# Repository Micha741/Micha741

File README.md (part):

# CircuitKit

Mobilní aplikace (React Native + Expo) pro elektroniky — databáze součástek, do budoucna
i návrh schémat obvodů a plošných spojů.

## Aktuální stav (MVP)

- **Databáze součástek** — lokální úložiště SQLite (`expo-sqlite`), běží celé na zařízení bez
  potřeby účtu nebo serveru.
  - Přidávání, úprava a mazání součástek
  - Pole: název, kategorie, výrobce, pouzdro, hodnota, počet kusů skladem, umístění,
    odkaz na datasheet, tagy, poznámky
  - Vyhledávání podle názvu / tagu / výrobce / hodnoty
  - Filtrování podle kategorie
  - **Výchozí knihovna běžných součástek** — při prvním spuštění se automaticky nahraje
    922 běžných součástek: 118 rezistorů (řada E12, 1 Ω – 8,2 MΩ; teplotní senzor Pt100; NTC
    termistory řady D-5 až D-25 pro omezení nárazového proudu; PTC termistory EPCOS/TDK
    B590** pro nadproudovou ochranu telekom linek; přesný tenkovrstvý SMD rezistor Yageo
    RT1206; obecná tlustovrstvá SMD čipová řada ROYALOHM (0201–2512, E-24/E-96); laserem
    in-circuit laditelná řada Susumu RT0603/RT0510/RT0816/RT1220; tenkovrstvá
    izolovaná rezistorová síť Vishay Dale TRA06E; kombinovaná rezistorová/kapacitní síť RCD
    Components RC0801-100J100J; a otočné potenciometry a trimry (lineární/logaritmické, THT/SMD)),
    51 kondenzátorů (keramické,
    elektrolytické, tantalové, fóliové; vysokonapěťová 1000V keramická disková řada NTE 90000;
    přesná keramická disková řada Multicomp MCBU/MCFU; nízko/vysokonapěťová keramická
    disková řada Illinois Capacitor GMR/GQR; NP0 disk Meritek CCNPO101J50V5B1; fóliová IGBT
    snubber řada Cornell Dubilier SCD; radiální tantalový kondenzátor RCD Components
    TRA10-103; vysokonapěťová 1250V fóliová řada Okaya HCPB; a širší vysokonapěťová fóliová řada
    Okaya HCP-S (450-1250V)), 232 diod
    (usměrňovací (včetně vysokonapěťové řady Diotec GP1120–GP1600, DO-41, 1200–6000V), spínací,
    Schottky (včetně extrémně malé 30V onsemi NSR01L30MX, pouzdro X3DFN2 0,62×0,32mm),
    Zenerovy (včetně SMD řady EIC SMZ25, SOD-123FL,
    3,0–200 V, 1,3 W, 46 hodnot),
    LED včetně výkonových SMD LED LUXEON Rebel, OSLON SSL 80, OSRAM TOPLED Black LO T64F/LR
    T66F (černé pouzdro pro VMS displeje) a OSRAM Mini TOPLED LY M67K, ploché LED displeje
    ROHM LD-201, LD-001 a LD-701, 7segmentové LED displeje AND Optoelectronics AND-5610,
    16segmentové
    alfanumerické displeje AND-8010-B a Yellow Stone BS-AA21RD/BS-CA21RD, Texas Instruments
    TIL302/303/304, bargraf displeje QT Optoelectronics MV53164/MV54164/MV57164, modrý
    jednomístný displej Everlight ELS-512UBWA, 3místné displeje Yellow Stone
    BT-M511RD/BT-N511RD a Everlight ELT-511USOWA, velkoformátový 2,3" displej Everlight
    ELS-2326SYGWA, obousměrné přepěťové ochrany TRISIL
    STMicroelectronics
    SMTPA62-320/SMP-0SCMC/SMP100MC/SMP100LC/SMP75, tripolární TLP140/200/270 a aktivní
    přepěťová/nadproudová ochrana CLP200M, tyristory SemiWell SCD4C60S a WeEn TYN50W/TYN80W-1600T
    (1600V vysokonapěťové SCR), triak WeEn BTA330 (30A Hi-Com, TO220/D²PAK), laserové diody
    Roithner LaserTechnik QL85H6S-A/B/C, QL78I6S-A/B/C, QL78F6S-A/B/C, QL78J6S-A/B/C a
    QL85J6S-A/B/C-L, proudově omezující dioda Diotec CL05M6F (5,6mA, SOD-123FL), a výkonový
    duální modul rychlých epitaxních diod IXYS DSEI 2x 61-04C/-06C (FRED, 2x60A, 400/600V,
    trr=35ns, miniBLOC/SOT-227B); SMD MiniMELF spínací diody Diotec LL4148/LL4150/LL4151/
    LL4448 (150-300mA, 50-100V, SOD-80C, elektrický ekvivalent 1N4148/1N4448 v DO-35); a SMD
    čipové (chip) diody DC Components CD4148W/CD4148WS/CD4148WT (1206/0805/0603, 100V/150mA,
    další ekvivalent 1N4148); a 7dílná řada SMD usměrňovacích diod se standardní dobou
    zotavení Diotec M1-M7 (50-1000V, 1A, SMA/DO-214AC, budget verze řady S1A-S1M); a duální
    (2 diody, společná katoda) SOT-23 diody Diotec BAV99/BAV99L (rychlé přepínání, trr<4ns,
    85/100V) a BAV199 (extrémně nízký svodový proud, IR<5nA); a výkonové šroubovací
    tyristorové moduly Semikron SEMIPACK 1 SKKT92 (2x SCR společná katoda), SKKT92B (2x SCR
    společná anoda) a SKKH92 (SCR+dioda, poloviční řízení), 800-1800V, ITAV 95A)), 19 můstků
    (SMD jednofázové usměrňovací můstky Diotec ABS2/ABS4/ABS6/ABS8/ABS10/ABS10-16, 200-1600V,
    pouzdro ABS; Diotec S40/S80/S125/S250/S380/S500, 80-1000V, pouzdro TO-269AA MiniDIL SLIM;
    a Fairchild/onsemi DF005S/DF01S/DF02S/DF04S/DF06S/DF08S/DF10S, 50-1000V/1,5A, pouzdro SDIP
    4L),
    86 tranzistorů (bipolární NPN/PNP (včetně onsemi rodiny BC817-16L/25L/40L, SOT-23), Darlington, duální, komplementární páry, výkonové, VF,
    MOSFET (včetně vysokonapěťového 600V/20A ISC H5N6001P, TO-3P, a duálního logic-level Nexperia BSS138PS, SOT363), IGBT (onsemi AFGB40T65SPD-BW,
    650V/40A Field Stop Trench, D²PAK, copackovaná rychlá dioda), JFET (včetně RF JFET rodiny
    Fairchild 2N5484/5485/5486 a SMD MMBF5484/5485/5486, SOT-23), IR fototranzistory Lite-On
    LTR-306 a LTR-1650D, fototranzistor pro viditelné
    světlo (náhrada CdS) Kodenshi PT23GP11), 170 integrovaných obvodů
    (časovače, komparátory, op-zesilovače, regulátory, logická hradla, čítače,
    Wi-Fi mikrokontroléry ESP32, ESP32-C3, ESP8285, ESP8684, Wi-Fi adaptér ESP8089, 8bit AVR
    mikrokontroléry ATmega640/1280/1281/2560/2561, rodina CAN mikrokontrolérů AT90CAN32/64/128
    (AVR) a T89C51CC01/02, AT89C51CC03 (8051), digitální teploměry DS18B20, DS1822, TC625,
    senzory vlhkosti a teploty DHT11, SHT71/SHT75, SHT85, CO2 senzory Sensirion SCD40/SCD41
    a kanálový (duct) senzor Belimo
    22DTH-51M, sériové flash paměti MX25L6406E a MX25L1026E, paralelní flash paměti řady
    MX29GL320E (T/B/H/L), USB-I2C most FT200XD, RS-485/RS-422 přijímače Renesas ISL32173E
    a příbuzné (ISL32175E/32177E/32273E/32275E/32277E), automotive TFT-LCD napájecí obvody
    Maxim MAX25220/MAX25221/MAX25221B/MAX25520, LCD-TV napájecí obvody Intersil/Renesas
    ISL97652 a ISL78010, TFT-LCD napájecí obvody E-CMOS EC9223 a Torex XC9516, senzory
    vlhkosti/teploty HOPERF TH10, PIR pohybové senzory Murata IRA-S410ST03, IRA-S230ST01 a
    kvadrátní IRA-S510ST01, plynový (SnO2) senzor ozónu Hanwei MQ-131, I2C senzory LITE-ON
    LTR-706PS-01 (proximity s VCSEL emitorem) a LTR-329ALS-01 (okolní osvětlení, duální kanál),
    piezoelektrické rázové/vibrační senzory Murata PKGS-00LDP1-R,
    PKGS-25WXP1-R a automotive TPMS PKGS-45TAV-R, zesilovací IC pro rázový senzor ROHM
    BD3852MUZ-Z, 6osý MEMS akcelerometr/gyroskop STMicroelectronics LSM330DL, jednoosý
    analogový křemenný automotive gyroskop Epson Toyocom XV-8000CB, a galvanicky oddělené
    proudové senzory ZMC10 (magnetorezistivní) a Allegro ACS752SCA-050/ACS754xCB-050/
    ACS754xCB-150/ACS755xCB-050 (Hallův jev), reflexní optický senzor Honeywell
    HOA0709-011, optické PPG senzory OSRAM SFH 7051 (tepová frekvence), SFH7050
    (tepová frekvence + SpO2) a SFH7060 (5 emitorů, tepová frekvence + SpO2), a proudové
    senzory CUI CSXX05B series aj.; izolovaný DC/DC měnič TRACO POWER TRA 1 Series; fototranzistorové
    optočleny LITE-ON LTV-356T (CTR 50-600%, Viso 3750Vrms, mini-flat SMD), Everlight EL817
    Series (CTR 50-600%, Viso 5000Vrms, DIP-4/SMD), Sharp PC817 Series (rank A-D, CTR 50-600%,
    Viso 5000Vrms, DIP-4), dvoukanálová řada Vishay ILD205T/206T/207T/211T/213T/217T (2 optočleny
    v pouzdře SOIC-8, BVCEO 70V, Viso 3000Vrms) a LITE-ON LTV-8X7 Series (LTV-817 1-kanálový
    DIP-4, LTV-827 2-kanálový DIP-8, LTV-847 4-kanálový DIP-16, Viso 5000Vrms, VCEO 35V);
    osmikanálové Darlingtonovy budiče ST ULN2801A/2802A/2803A/2804A (500mA/kanál, 50V, DIP-18,
    liší se vstupním odporovým děličem pro různé logické rodiny); hardwarový TCP/IP Ethernet
    kontrolér WIZnet W5500 (SPI, 32KB buffer, 8 hardwarových socketů, LQFP-48); napěťové
    supervizory (reset obvody) TI TPS3809J25/L30/K33/I50 (prahy 2,25/2,64/2,93/4,55V, SOT-23-3,
    pin-kompatibilní s MAX809); nízkopříkonový CMOS časovač ST TS555 (pinově kompatibilní s
    NE555, 110µA typ., max. 2,7MHz); 16bitový nízkopříkonový MCU TI MSP430G2553 (16KB Flash,
    512B RAM, ADC10, USCI UART/SPI/I2C, základ LaunchPad kitu); 32bitový Arm Cortex-M0+ MCU
    TI MSPM0L1306 (64KB Flash, 4KB RAM, 12bit 1,68Msps ADC, 2x OPA, GPAMP, COMP, UART/I2C/SPI);
    starší 16bitový MCU TI MSP430F149 (60KB Flash, 2KB RAM, ADC12, 2x USART, hardwarová
    násobička, 48 I/O); nejmenší MSP430 MSP430F1121A (4KB Flash, 256B RAM, 14 I/O, jen
    komparátor bez ADC, 20/24pinové pouzdro); z katalogu HOPERF Catalog 2020: RF vysílací/
    přijímací IC řada CMOSTEK CMT2xxx (27-1020MHz, OOK/(G)FSK/MSK), tlakové senzory HOPERF
    HPxxx/HP5xxx Series (300Pa-2000kPa, I2C/SPI) a levnější sesterské senzory vlhkosti/teploty
    TH08, TH06 a teplotní senzor T06 (SOT23-5, bez vlhkosti) k již evidovanému TH10; a plně
    digitální Class-D zesilovače reproduktoru s DSP ROHM BM28720MUV (20W+20W) a BM28723MUV
    (17W+17W, output feedback, bez snubberu); a digitální barometrický tlakový senzor Bosch
    BMP280 (I2C/SPI); kombinovaný digitální senzor vlhkosti/tlaku/teploty Bosch BME280
    (I2C/SPI, registrově kompatibilní s BMP280); neregulovaný izolovaný DC/DC měnič RECOM
    ECONOLINE REZ Series; trojitý single-supply video buffer s nábojovou pumpou Renesas/Intersil
    ISL59837 (16 Ld QSOP); 12dílná rodina LDO regulátorů NIKO-SEM L1117 (SOT-223/TO-220/TO-252/
    TO-263, pevné 2,5-5V i nastavitelné); 9dílná rodina nízkoproudých LDO regulátorů Fairchild
    KA78LXXA (TO-92, 5-24V); kompletní napájecí řadič pro DDR2/DDR3/DDR3L/LPDDR3 paměti Texas
    Instruments TPS51716 (buck + VTT LDO + VTTREF, 20-pin QFN); 1/4" SOC VGA NTSC/PAL CMOS
    obrazový senzor Micron MT9V135C12STC (48-pin CLCC, kompozitní video/LVDS/CCIR656); a
    kombinovaný PFC + half-bridge řadič předřadníku zářivek International Rectifier IRS2580DSPbF
    ("COMBO8", 8pin SOIC); a napájecí spínač (load switch) se soft-startem onsemi NCP330MUTBG
    (RDS(on) 26mΩ, 3A, UDFN4)),
    161 modulů
    (Wi-Fi/BLE: ESP32-C3-MINI-1, ESP32-C3-WROOM-02, Adafruit Feather
    HUZZAH ESP8266, ESP8684-MINI-1, ESP-12S; nízkonapěťové odpojovače baterie Alfatronix
    PowerTector PT10/PT20/PT40/PT60/PT100/PT200; LoRaWAN senzor LEO-S55 a brány USM-S67;
    solární bezdrátové senzory EnOcean ETHSA/ETHSU; 6,86" IPS TFT LCD moduly AZ Displays
    ATM0680L2A-CT s kapacitním dotykem a ATM0680L2A bez dotyku; a polohové displeje vřetene
    Baumer IVO N 142/N 152; znakový LCD modul PICVUE PVC200403; křemenné tlakové senzory
    Seiko Epson TSU-20G/TSU-70G/TSU-100G; evaluační deska ROHM RPR-0521RS-EVK-001 pro
    kombinovaný senzor přiblížení/okolního osvětlení; optoelektronické snímače přiblížení SICK
    WTB250-2N1131/WTB250-2N1151; wearable zdravotní senzorový náramek Maxim MAXREFDES103#
    s optickým PPG biosenzorem; MEMS tlakový senzorový modul Hokuriku HPM-100GD-A01; a
    indukční přibližovací spínače TURCK BI1.5U-EG08-RP6X-H1341 (uprox Factor 1) a
    BI1-EG05K-AN6X-V1331 (klasický feritový); radarové senzory pohybu Banner R-GAGE
    Q130RA (FMCW) a Pepperl+Fuchs RaDec-M, RAVE-D-NA, RMS-G-RC a RMS-M-RC (Dopplerovy, relé
    výstup(y), rozlišení osob/vozidel u RAVE-D-NA/RMS-G-RC); a kapacitní přibližovací
    spínače TURCK BC10-PT30-AZ3X, BC10-Q14-VN4X2,
    BC10-QF5.5-RN6X2, BC20-Q20-RZ3X2, BC20-Q20-AN4X2/S400 (DC verze, kabel) a
    BC20-Q20-AN4X2-H1141 (DC verze, M12 konektor); a indukční přibližovací spínač Pepperl+Fuchs
    NBB1-4GM22-E0, NBB2-8GM25-E0-V3, NBB2-8GM25-E2-V3, NBB2-8GM40-E2-V1, NBB2-8GM50-E0,
    NBB2-8GM50-E2-5M, NBB2-8GS35-E2-V1, NBB2-8GS40-E2-5M-PUR, NBB2-12GM60-A2, NBB3-V3-Z4,
    NBB4-12GM30-E2-V3, NBB4-12GM30-E3, NBB4-12GM35-A2-V1-M1 (automotive),
    NBB4-12GM50-E2-3G-3D (ATEX), NBB4-12GM75-US, NBB5-18GM40-Z0-V1, NBB8-18GM50-E2,
    NBB10-30GM50-E0, NBB10-30GM50-E2-C3-V1, NBB20-L3M-A2-C3-V1 (svařovací "Weld Immune") a
    NBB20-U1-A2-T (otočná hlava, VariKont), NBN3-F31K-E8-K (dvoukanálová jednotka pro
    pneumatické pohony s výstupem pro solenoidový ventil), NEN6-8GM40-E2-PUR (nezápustný
    typ), NBB8-18GM50-A0-V1-M1 (automotive M18), NBB15-30GM50-E0-M-Y242746 (M30, NPN, E1
    homologace, -40 až +85 °C), NBN8-12GM50-E2-V1-Y323749 (nezápustný M12, konektor) a
    NBN40-U1-E0-M (otočná hlava VariKont, 40mm, nezápustný, E1, 10-60V) a
    NJ4-12GM-N-5M-Y123257 (NAMUR výstup, ATEX jiskrově bezpečný, zóna 20); a kapacitní přibližovací
    spínače Pepperl+Fuchs CBB4-12GH60-E0-V1 (potravinářský, nerez 316L, NPN) a CBB4-12GH60-E2-V1
    (potravinářský, nerez 316L, PNP) a CBB8-18GS75-E2 (M18, nastavitelný rozsah 1-8mm, kabel);
    a fotoelektrická jednocestná závora
    (through-beam pár vysílač+přijímač) SICK GRSE18S-N2421V (GR18 Inox); reflexní fotoelektrický
    senzory s IO-Link Pepperl+Fuchs OBG4000-R103-2EP-IO, OBG5000-R100-EP-IO-V3 a
    OBG5000-R101-2EP1-IO (detekce transparentních objektů); a MIPI CSI-2 kamerový
    modul Leopard Imaging LI-OS05A20-MIPI-110H (OmniVision OS05A20, 5 Mpx); průmyslový vizuální
    senzor (smart kamera) Festo SBSC-U-AF-R2B (čtení kódů, OCR, Ethernet), vizuální senzor pro
    polohování regálových zakladačů Pepperl+Fuchs PHA400-F200A-B17-V1D a PHA400-F200-B17-V1D
    (PROFINET, liší se jen orientací konektorů) a barevný vizuální
    senzory Festo SBSI-F-R3C-F6-W a SBSI-F-AF-R3C-F12-W (integrovaná optika/osvětlení, plná
    kapacita) a monochromní objektový senzor Festo SBSI-Q-AF-R2B-F12-W; a polohové snímače
    pístu pneumatického válce Festo SME-8M-DS-24V-K-5,0-OE (magnetický jazýčkový kontakt),
    SMT-8M-A-PS-24V-E-0,3-M8D, SMT-8M-A-PS-24V-E-2,5-OE, SMT-8M-A-PS-24V-E-0,3-M12
    (magnetorezistivní) a SMT-8M-A-ZS-24V-E-5,0-OE-EX2 (magnetorezistivní, ATEX, 2vodičové), a
    svařovací pole odolný Festo SDBT-BSW-1L-PU-W-0.3-N-M12 (magnetorezistivní, weld-resistant) a
    SME-8-K5-LED-24 (reed, podélné upnutí, otevřený konec kabelu) a SME-8-S-LED-24 (reed,
    podélné upnutí, M8 konektor), SMEO-8E-K-24-S6 (reed, vysokoteplotní -40 až +120 °C, montáž
    příslušenstvím), SMEO-8E-M12-LED-24 (reed, integrovaný konektor M12, hliníkové pouzdro) a
    SMEO-8E-M12-LED-230 (reed, integrovaný konektor M12, univerzální 3-230V AC/3-250V DC) a
    SMPO-8E (čistě pneumatický 3/2 ventil bez elektrického připojení, ATEX zóny 1/2/21/22) a
    SMTSO-8E-NS-M12-LED-24 (magnetoindukční, NPN, svařovací pole odolný) a
    SMT-10G-PS-24V-E-2,5Q-OE (magnetorezistivní, pro kruhovou drážku) a
    SME-10M-ZS-24V-E-2,5-Q-OE (reed, 2vodičové, pro kruhovou drážku) a Festo SIEH-3B-PS-S-L
    (obecný miniaturní indukční spínač Ø3 mm) a SPAN-B11R-M5F-PNLK-PNVBA-L1 (tlakový senzor s
    displejem, IO-Link), SPAN-B-B11R-R18M-PN-L1+2.5S (tlakový senzor s displejem, "Basic",
    1 výstup), SDE5-D10-C3-Q6E-P-K (tlakový spínač bez displeje, QS-6, integrovaný kabel) a
    SDE5-D10-C-Q4E-P-M8 (tlakový spínač bez displeje, QS-4, M8 konektor) a SDE5-D10-NF-Q6E-V-K
    (analogový tlakový snímač 0-10V, bez spínacího výstupu, integrovaný kabel) a
    SDE5-D10-NF-Q6E-V-M8 (analogový tlakový snímač 0-10V, M8 konektor), SDE5-D10-O-Q6E-P-M8
    (tlakový spínač bez displeje, N/O, QS-6, M8) a SDE5-V1-NF-Q6-V-M8 (analogový vakuový snímač
    0 až -1 bar, M8) a SPAN-B11R-M5F-PN-PN-L1 (tlakový senzor s displejem, 2 výstupy, bez
    analogu a IO-Link), SPAW-P100R-G12M-2N-M12 (vysokotlaký tenkovrstvý senzor 0-100 bar,
    celokovový), SPAW-B11R-G14F-2P-M12 (tenkovrstvý senzor -1 až 10 bar, celokovový) a
    SPAW-B2R-G12M-2P-M12 (piezorezistivní senzor -1 až 1 bar, celokovový) a
    SPAW-B11R-G14F-2N-M12 (tenkovrstvý senzor -1 až 10 bar, celokovový, NPN) a
    SPAW-P100R-G14F-2N-M12 (vysokotlaký tenkovrstvý senzor 0-100 bar, celokovový, G1/4) a
    SPAW-P50R-G12M-2N-M12 (vysokotlaký tenkovrstvý senzor 0-50 bar, celokovový),
    SPAW-P25R-G12M-2NV-M12 (0-25 bar, spínací + analogový výstup současně), optický senzor
    prachu/PM2.5 Winsen ZPH02 a ATEX senzorová skříň polohy ventilu Festo
    SRBE-CA3-YR90-MW-22A-1W-C2M20-EX (mechanický přepínací spínač), RGB segment signálního
    majáku Banner SG-TL70-RGB14, programovatelný zvukový segment Banner SG-TL70-AP (MP3/WAV) a
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
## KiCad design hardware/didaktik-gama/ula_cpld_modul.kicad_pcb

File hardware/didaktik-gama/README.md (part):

# Didaktik Gama – schéma zapojení v KiCadu

Překresleno z tištěné předlohy „DIDAKTIK GAMA – SCHÉMA ZAPOJENIA“.

| Soubor | Obsah |
|---|---|
| `didaktik_gama.kicad_pcb` | plošný spoj hlavní desky 300 × 225 mm, 4 vrstvy – rozmístěno, nety přiřazeny, **cesty signálů zatím nevedené** |
| `didaktik_gama_pcb_nahled.pdf` | náhled rozmístění desky |
| `gen_pcb.py` | generátor desky z `netlist.py` (`python3 gen_pcb.py`, potřebuje KiCad s modulem pcbnew) |
| `ula_cpld_modul.kicad_pcb` / `_pcb_nahled.pdf` | plošný spoj modulu ULA 70 × 50 mm, 2 vrstvy – rozmístěno, nety přiřazeny, cesty nevedené |
| `gen_pcb_modul.py` | generátor desky modulu (`python3 gen_pcb_modul.py`) |
| `make_fab.py` | výrobní podklady: gerbery, vrtání, soupis součástek, souřadnice osazení, ZIP (do `vyroba/`) |
| `gama.pretty/`, `fp-lib-table` | vlastní pouzdro Raspberry Pi Pico (THT 2×20) |
| `didaktik_gama.kicad_sch` / `.kicad_pro` | schéma pro KiCad 8 a novější (A0, jedna strana, vlastní knihovna symbolů je v souboru) |
| `didaktik_gama_nahled.pdf` / `.svg` | náhled bez KiCadu |
| `netlist.csv` | všechny nety a piny (`U1.30` = U1 pin 30) |
| `bom.csv` | soupis součástek |
| `k_overeni.csv` | místa, která jsou na předloze nečitelná nebo odhadnutá |
| `netlist.py` | **zdroj pravdy** – netlist ručně přepsaný z předlohy |
| `gen.py` | generátor: `python3 gen.py` vše znovu vytvoří, `python3 gen.py modul` vytvoří modul ULA |
| `ula_cpld_modul.kicad_sch` / `.kicad_pro` / `_nahled.pdf` | modul náhrady ULA s CPLD XC95144XL (TQ100) do patice U4 |
| `ula_cpld_modul.ucf` | přiřazení pinů CPLD pro firmware (Xilinx ISE) |
| `netlist_modul.py`, `*_modul.csv` | netlist, soupis a body k ověření modulu |

Spoje jsou vedeny návěštími (labels): stejné jméno = stejný net. `/X` v netlistu
(v KiCadu `~{X}`) znamená signál aktivní v nule. Oprava spoje = změna jména netu
v `netlist.py` a nové spuštění `gen.py`, nebo přejmenování návěští přímo v KiCadu.

Napájení (konektor J5, pojistka F1, ochranná dioda D12, MA7805 U32, filtrace a blokovací
kondenzátory 100n u každého IC) na předloze není – je doplněno a vedeno v `k_overeni.csv`.

Pinouty UA880D, 27128, 8255, 4164, 2118 a 74LS157 odpovídají katalogovým listům
a souhlasí s čísly na předloze. ULA je očíslovaná podle předlohy (shodné se ZX ULA).

## Plošný spoj hlavní desky
- **Rozměr 300 × 225 mm, 4 vrstvy:** F.Cu a B.Cu pro signály, In1.Cu = celoplošná **GND**, In2.Cu =
  celoplošná **+5V**. Napájení všech vývodových součástek je tím propojené bez cest.
- **Rozmístění po blocích:** konektory na horním okraji (napájení, MG, jack, reproduktor, VGA,
  klávesnice, porty 8255) → CPU / ROM / 8255 / patice ULA → multiplexery a logika → 8× 4164 →
  8× 2118 → zvuk (YM2149, LM386), USB klávesnice (Pico), napájení. Blokovací kondenzátory u každého IC.
- **Kontrola DRC:** žádné překryvy pouzder ani chyby obrysu; zbývá **499 nepropojených spojů** (cesty
  signálů + napájení SMD obvodů U40/U41, které potřebují prokovy do vnitřních vrstev).

### Dokončení (vedení cest)
1. Otevřít `didaktik_gama.kicad_pro` v KiCadu 8/9 (soubor desky je ve formátu KiCadu 7, otevře se).
2. Automaticky: **Freerouting** (plugin v KiCadu nebo File → Export → Specctra DSN, výsledek
   File → Import → Specctra Session). Pravidla: cesta 0,25 mm, mezera 0,2 mm, prokov 0,6/0,3 mm;
   napájecí cesty (VIN, SPK_OUT) ručně 0,6–1 mm.
3. Zkontrolovat orientaci konektorů na hraně (VGA, jack, napájecí konektor) ve 3D náhledu.
4. Po začátku vedení cest už **nespouštět `gen_pcb.py`** (přepíše desku) – změny ze schématu přenášet
   v KiCadu přes *Update PCB from Schematic*.

## Plošný spoj modulu ULA
- **70 × 50 mm, 2 vrstvy**, zem rozlitá z obou stran (F.Cu i B.Cu).
- **J1** = 40 kolíků v rozteči DIP-40 (600 mil), zespodu do patice U4; pin 1 vlevo dole (čtvercová ploška).
  Mezi řadami kolíků jsou SMD součástky (stabilizátor U2, oscilátor X1, odpory) – J1 má proto vymezení
  jen kolem řad kolíků. Použít precizní (soustružené) kolíky.
- **U1** XC95144XL (TQFP-100) nad horní řadou kolíků, blokovací kondenzátory u napájecích vývodů.
- **J2** vlevo (RGB + zvuk + napájení, kabel 1:1 na J8 hlavní desky), **J3** JTAG vpravo.
- Modul přesahuje patici: na hlavní desce zabírá plochu 70 × 50 mm nad U4. J8 je proto u pravé hrany;
  pod modulem smí být jen nízké součástky (odpory, keramické kondenzátory).
- DRC: bez překryvů; zbývá 76 nepropojených spojů (cesty) a 2 zemní plošky CPLD s jedním
  tepelným můstkem – vyřeší se při vedení cest (prokov k zemi u vývodu).

## Výrobní podklady (gerbery)
Až budou obě desky natrasované a DRC v KiCadu čisté:
```bash
python3 make_fab.py            # obě desky
python3 make_fab.py modul      # jen modul ULA
```
Vznikne `vyroba/<deska>/`: `<deska>_gerber.zip` (gerbery + vrtání, nahrát výrobci), `gerber/` (jednotlivé
vrstvy, mapy vrtání PDF, job soubor), `<deska>_bom.csv` (soupis ve formátu Comment/Designator/Footprint),
`<deska>_pozice.csv` (souřadnice pro strojní osazení) a `PARAMETRY.txt` (parametry objednávky).

**Pojistka:** skript nejdřív spustí DRC; pokud deska má nevedené cesty nebo chyby, export odmítne
(gerbery by daly nefunkční desku). `--force -o DIR` vytvoří zkušební export s varováním NEVYRÁBĚT.

| Deska | Parametry objednávky |
|---|---|
| hlavní | 300 × 225 mm, 4 vrstvy (In1 GND, In2 +5V), FR-4 1,6 mm, Cu 35 µm, HASL bezolovnatý / ENIG |
| modul ULA | 70 × 50 mm, 2 vrstvy, FR-4 1,6 mm, ENIG doporučeno (TQFP s roztečí 0,5 mm) |

## Návod pro Windows

### 1. Programy
| Program | K čemu | Odkud |
|---|---|---|
| **KiCad 10** (stabilní; případně 9) | schéma, desky, trasování, gerbery; obsahuje i Python s modulem `pcbnew`. **Ne vývojovou verzi 10.99** – ta Python/`pcbnew` nemá | https://www.kicad.org/download/windows/ |
| Git for Windows (volitelně) | stažení repozitáře, Git Bash pro skripty `.sh` | https://git-scm.com/download/win |
| Freerouting (volitelně) | automatické vedení cest – v KiCadu *Plugin and Content Manager* → „Freerouting“ | správce doplňků KiCadu |
| **Java 25+** (pro Freerouting) | Temurin JRE 25, Windows x64 .msi; v instalátoru zapnout *Set JAVA_HOME* a *Add to PATH*, pak restartovat KiCad (`java -version` musí ukázat 25+) | https://adoptium.net/temurin/releases/?version=25 |

Repozitář stáhněte přes *Code → Download ZIP* na GitHubu (nebo `git clone`) a rozbalte například do
`C:\gama`. Dále se pracuje ve složce `C:\gama\hardware\didaktik-gama`.

### 2. Dávkové soubory (dvojklik)
Soubory `.bat` samy najdou Python, který dodává KiCad (`C:\Program Files\KiCad\10.0`, `9.0` nebo `8.0`).

| Soubor | Co udělá |
|---|---|
| `vyroba.bat` | výrobní podklady do `vyroba\` (stejně jako `make_fab.py`; lze `vyroba.bat modul`, `vyroba.bat --force -o C:\test`) |
| `schema.bat` | znovu vytvoří schémata, netlisty, BOM a seznam k ověření z `netlist.py` / `netlist_modul.py` |
| `deska.bat` | znovu vytvoří obě desky z netlistu – **přepíše natrasované cesty**, proto se ptá |

Ručně lze totéž spustit z nabídky Start → **KiCad Command Prompt** (má v cestě `python` i `kicad-cli`):
```bat
cd /d C:\gama\hardware\didaktik-gama
python make_fab.py
```

### 3. Postup od desky k objednávce
1. Dvojklik na `didaktik_gama.kicad_pro` → otevře se KiCad; otevřít editor desky.
2. Trasování: *Tools → External Plugins → Freerouting* (nebo *File → Export → Specctra DSN*, ve Freeroutingu
   *Autorouter*, pak *File → Import → Specctra Session*). Totéž pro `ula_cpld_modul.kicad_pcb`.
3. *Inspect → Design Rules Checker* → opravit chyby, nepropojené spoje musí být 0.
4. Dvojklik `vyroba.bat` → ve `vyroba\hlavni\` a `vyroba\modul\` jsou ZIPy pro výrobce a `PARAMETRY.txt`.

### 4. Firmware na Windows
- **Pico (USB klávesnice a kazety):** instalátor *Raspberry Pi Pico* pro Windows nebo rozšíření
  *Raspberry Pi Pico* ve VS Code (obsahuje Pico SDK, CMake a překladač). Otevřít složku
  `firmware\pico-usb-kbd`, přeložit, `gama_usb_kbd.uf2` zkopírovat na disk RPI-RP2 (Pico s BOOTSEL).
  Testy na PC (`test\run_tests.sh`) jdou v Git Bash s překladačem `gcc` (např. z MSYS2) nebo ve WSL.
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
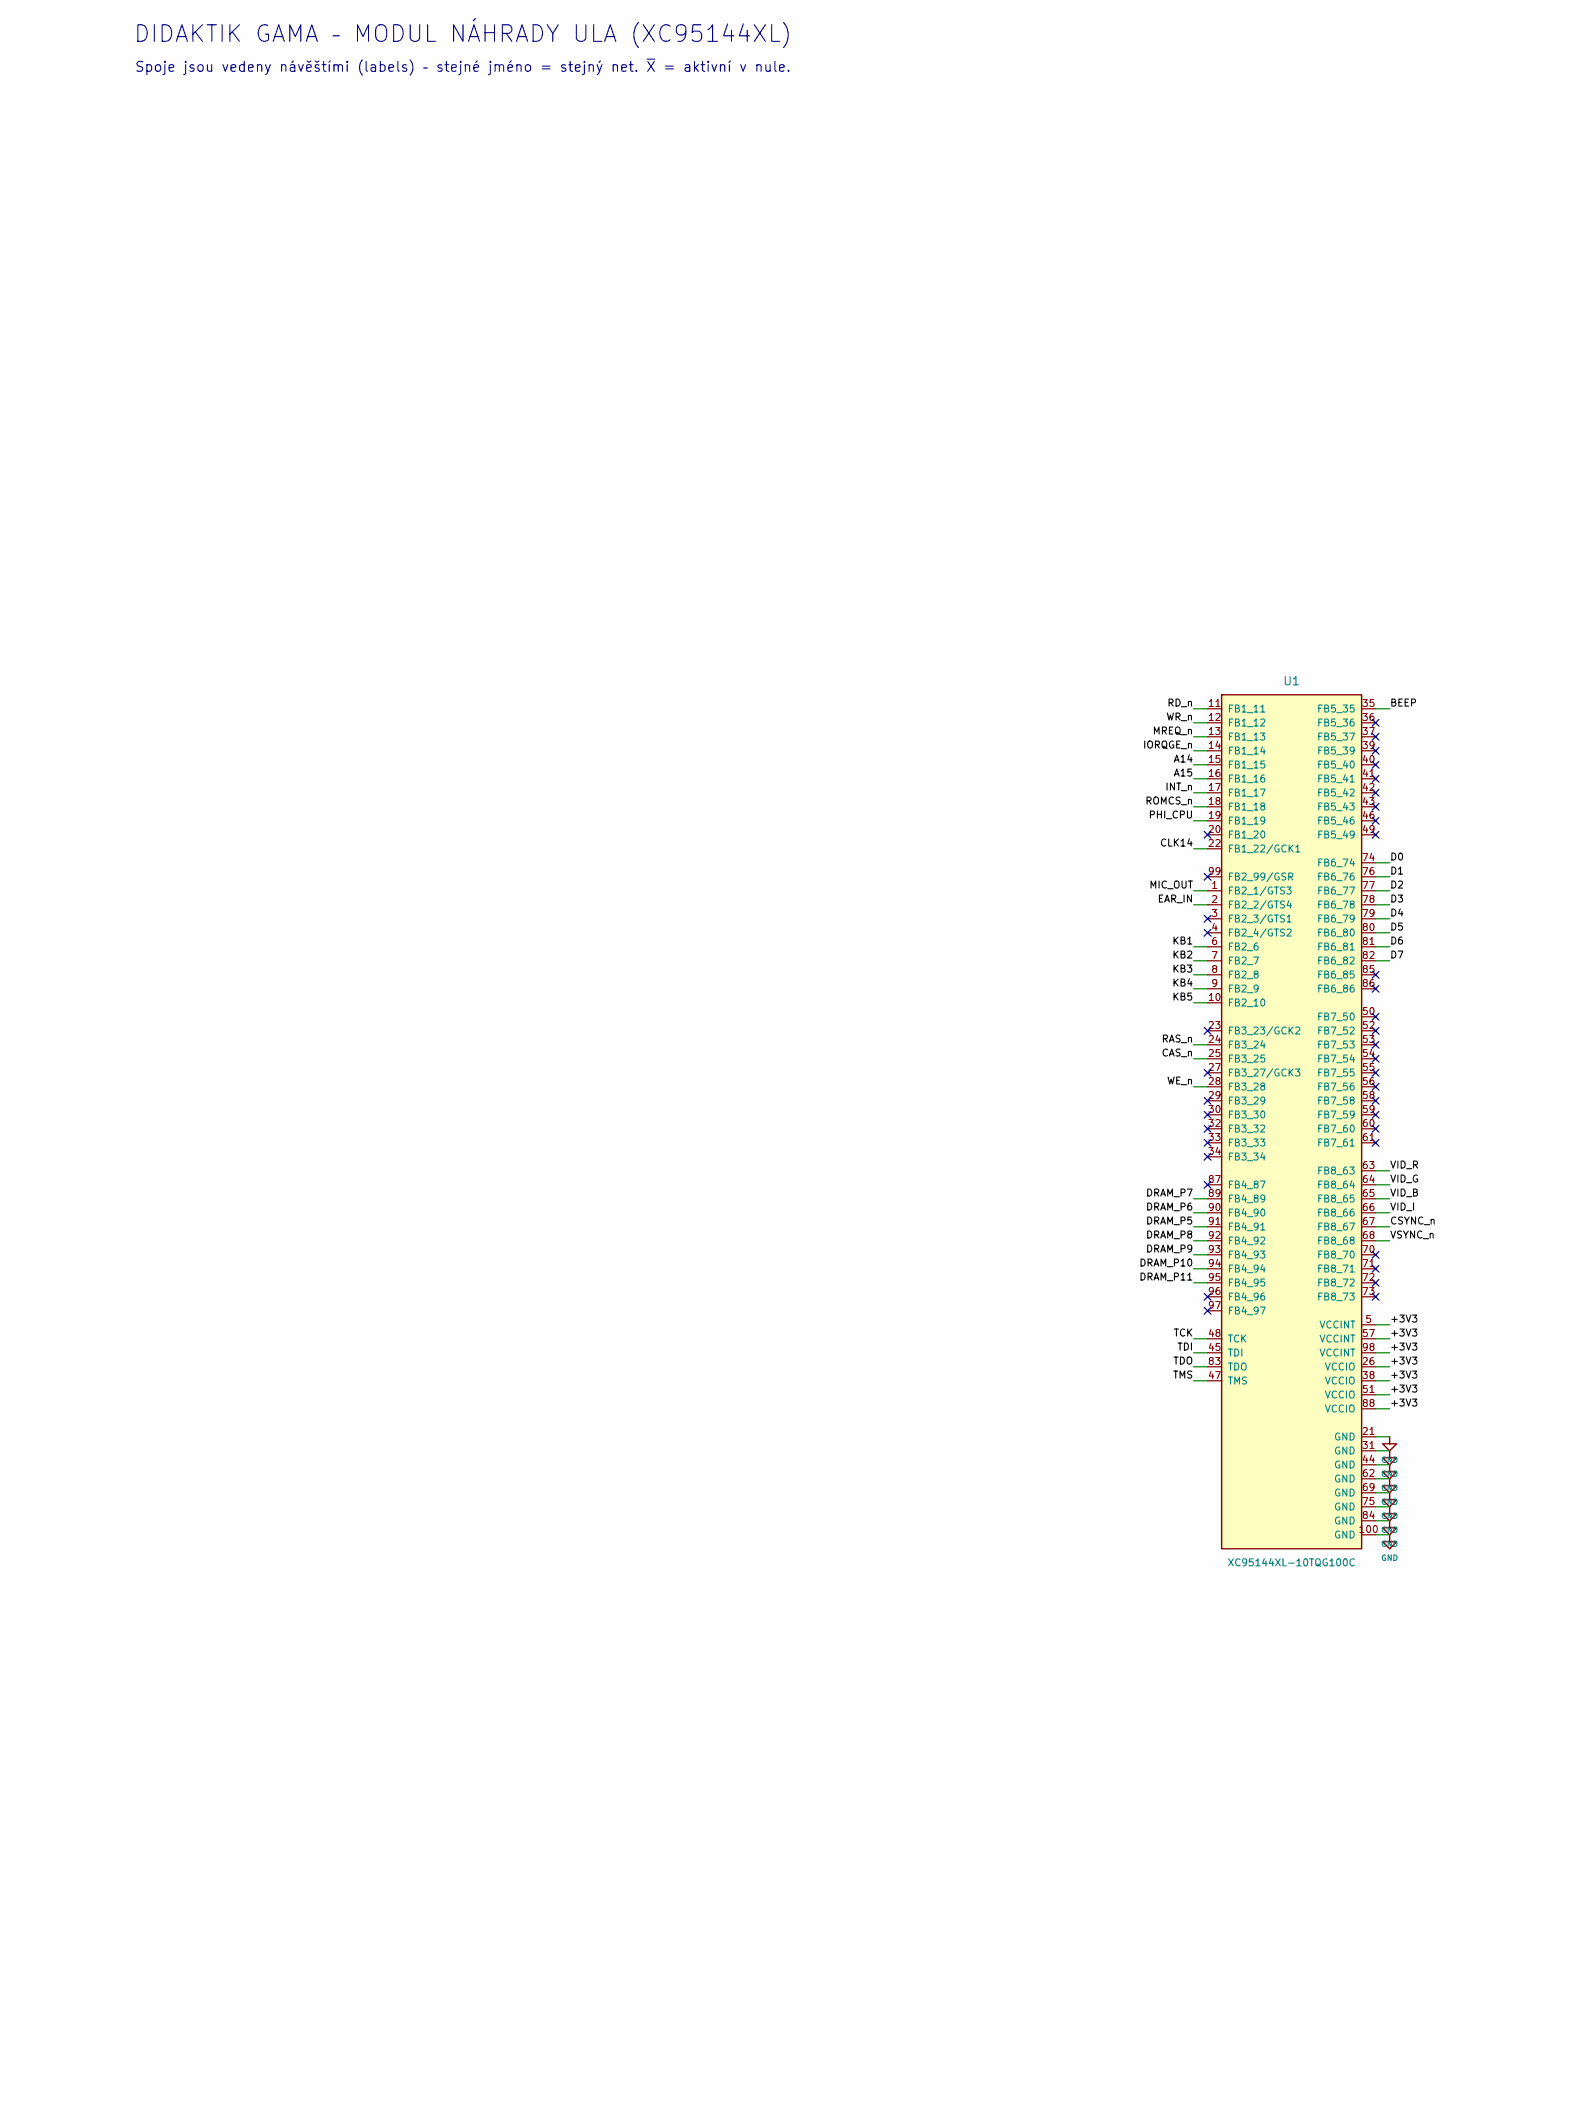
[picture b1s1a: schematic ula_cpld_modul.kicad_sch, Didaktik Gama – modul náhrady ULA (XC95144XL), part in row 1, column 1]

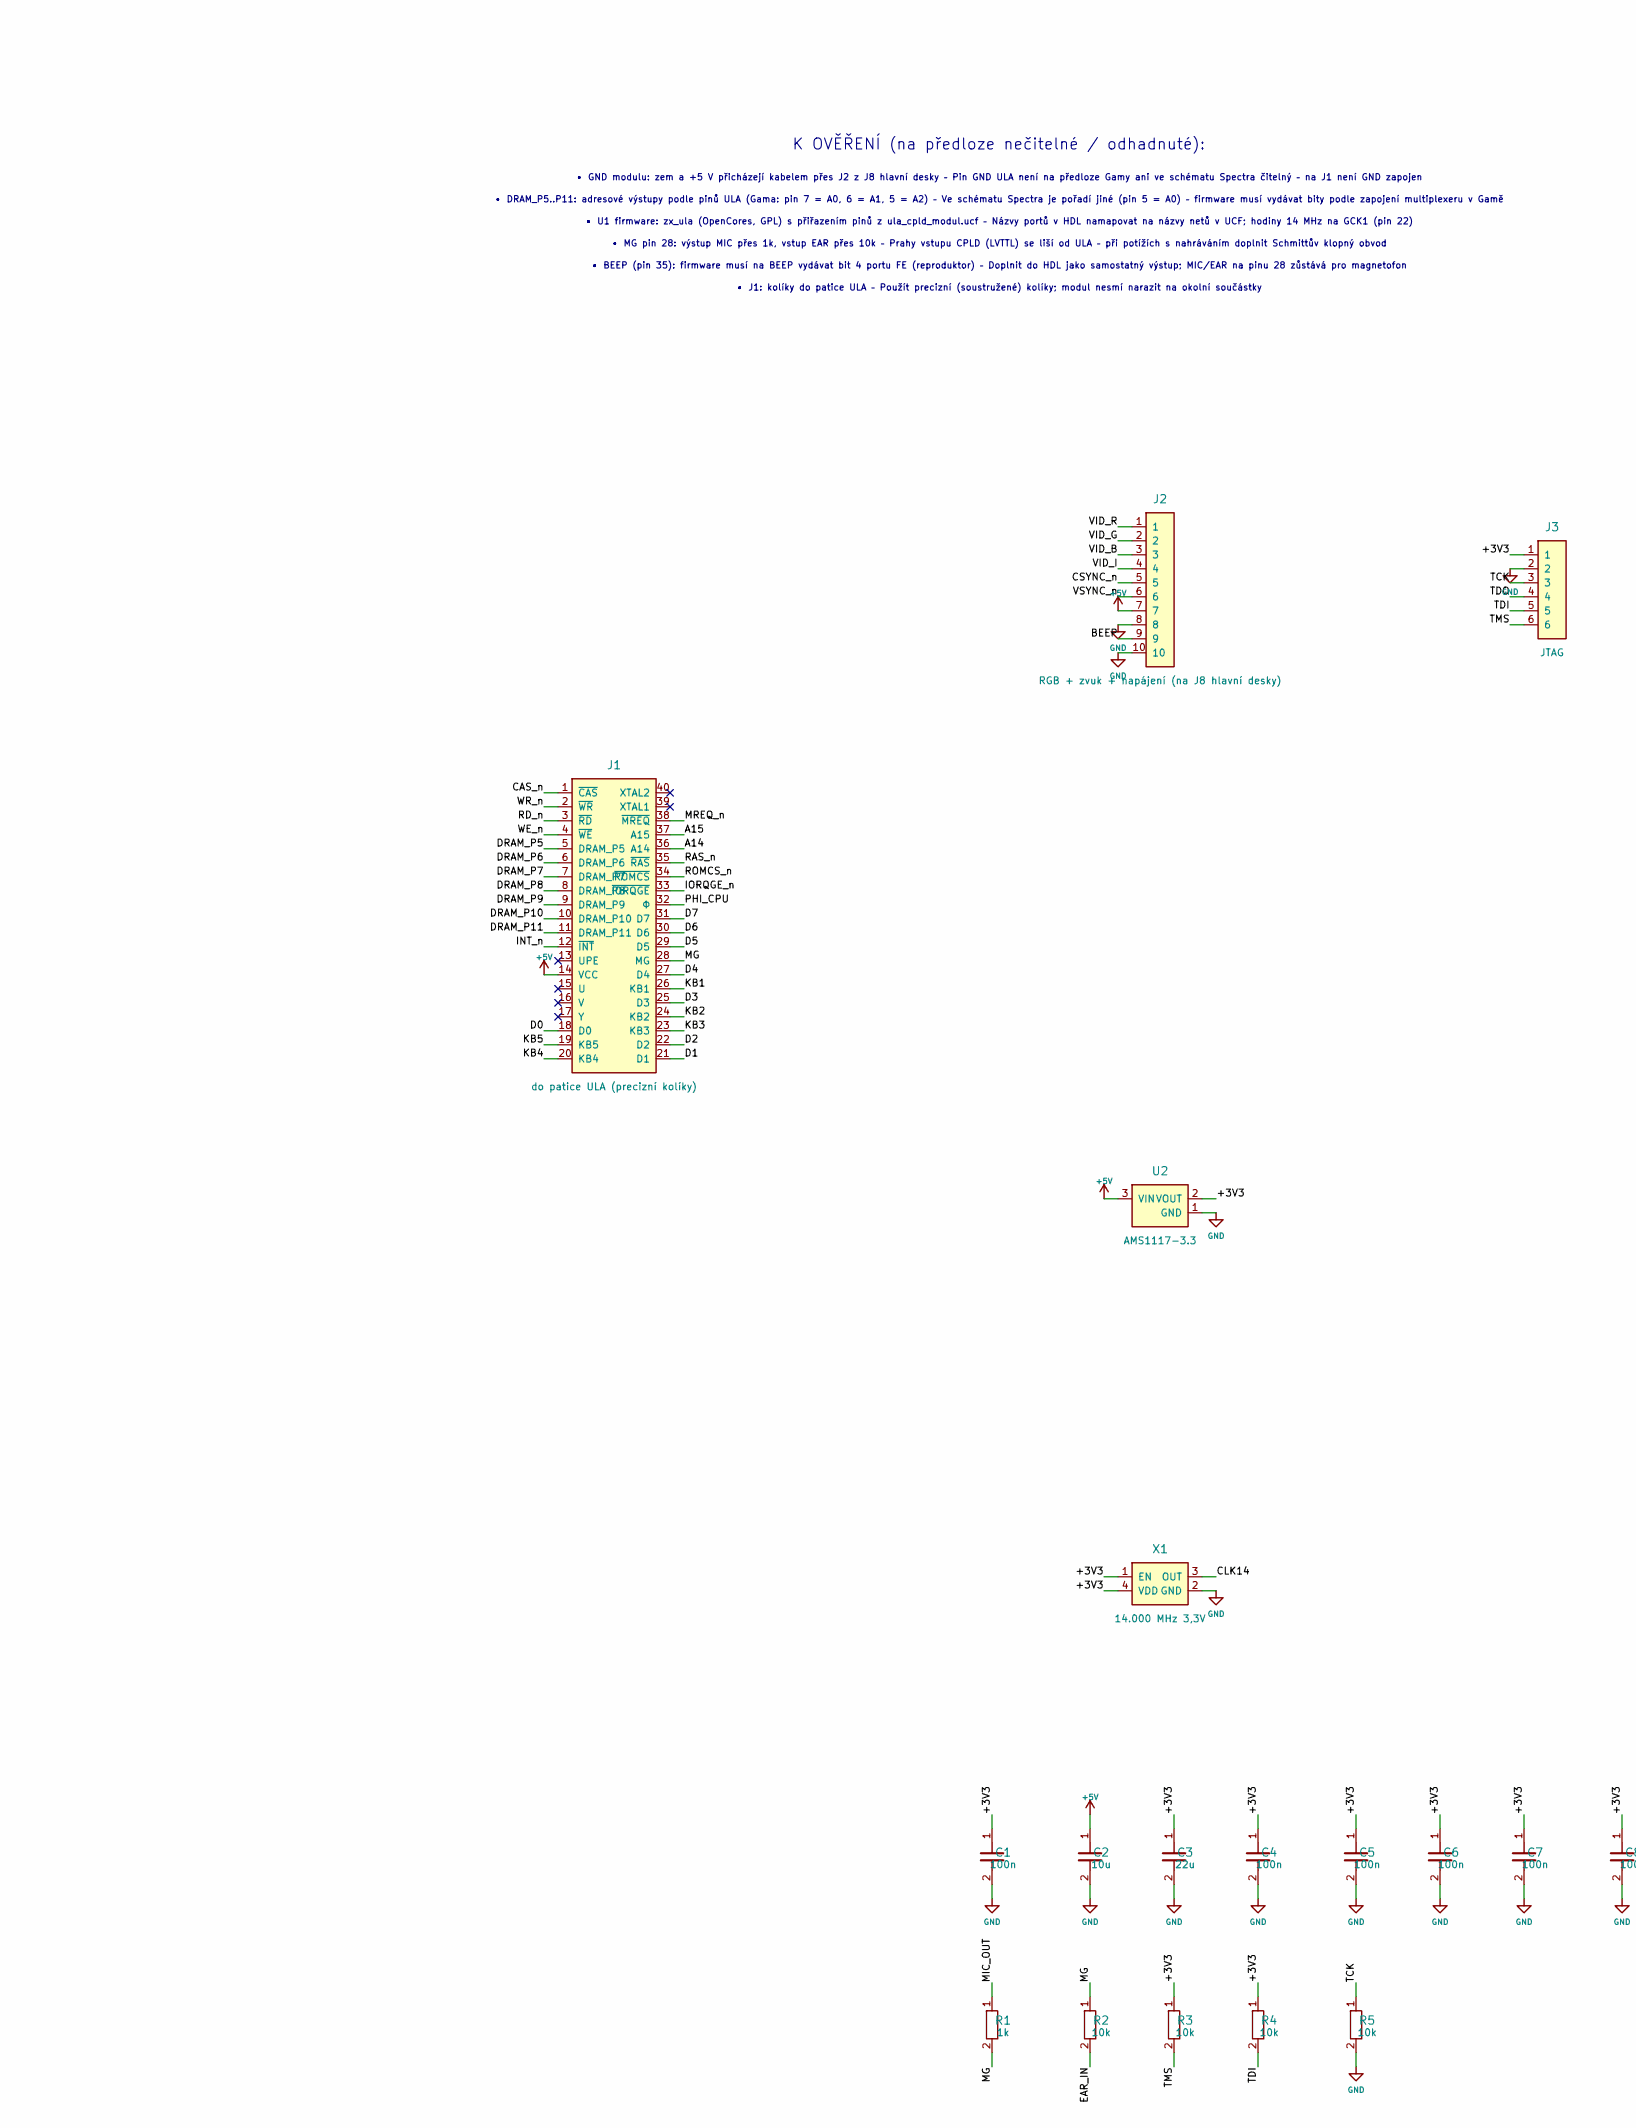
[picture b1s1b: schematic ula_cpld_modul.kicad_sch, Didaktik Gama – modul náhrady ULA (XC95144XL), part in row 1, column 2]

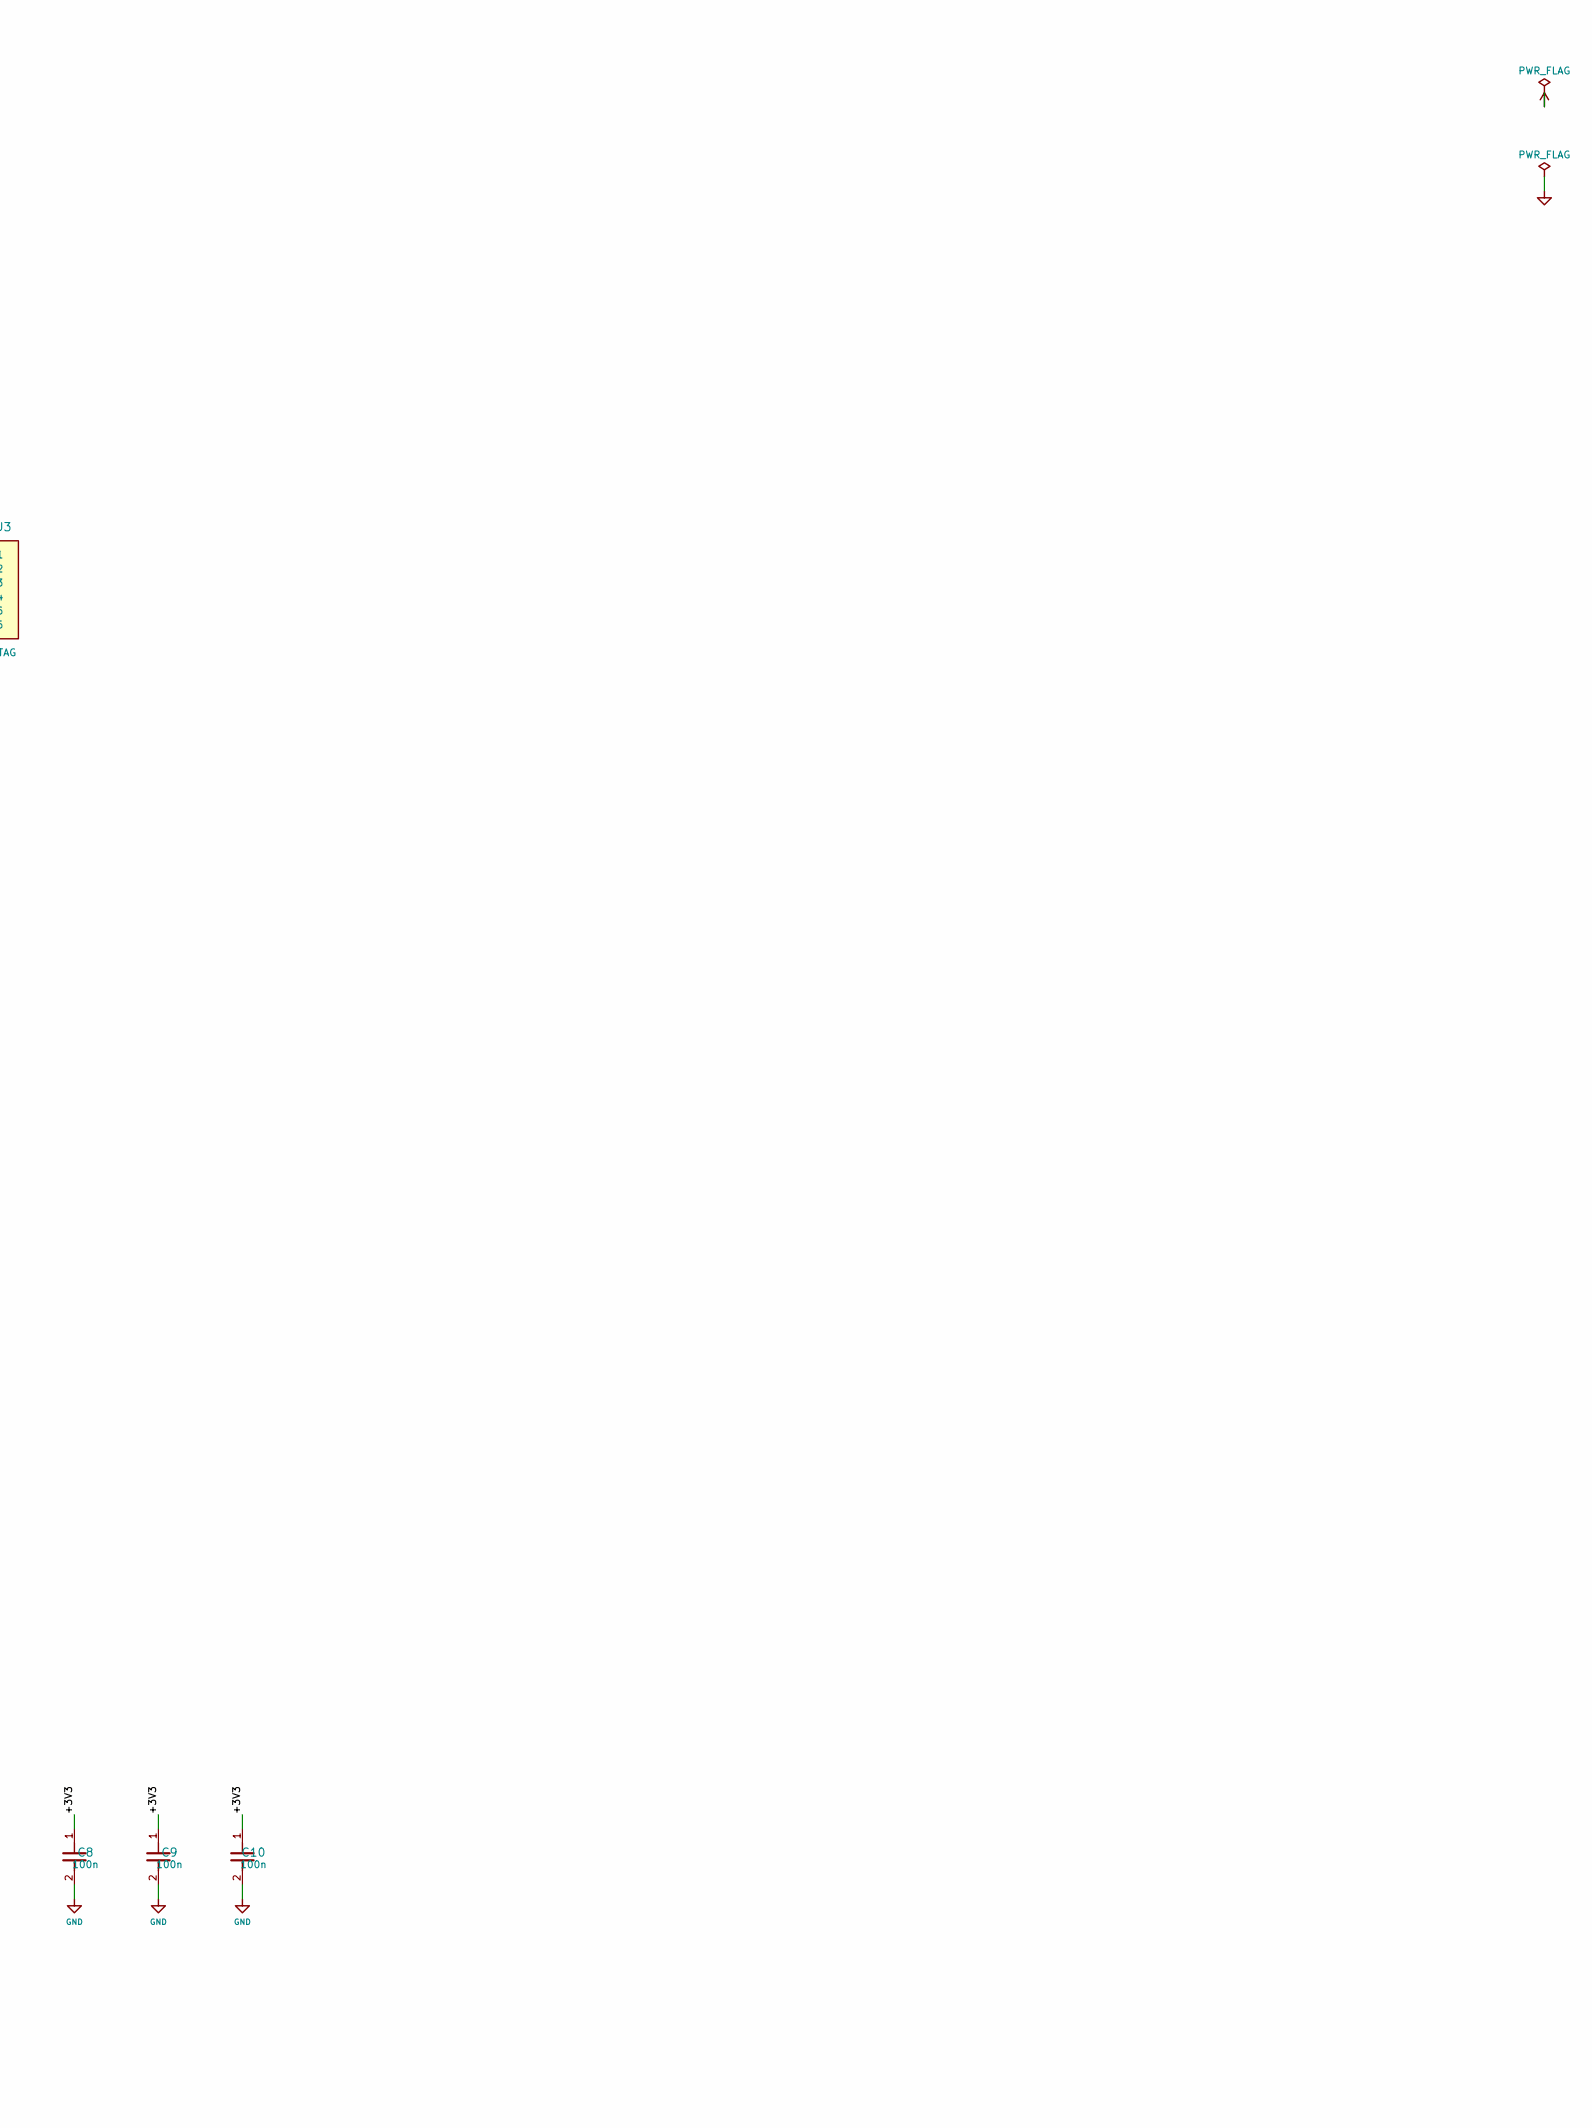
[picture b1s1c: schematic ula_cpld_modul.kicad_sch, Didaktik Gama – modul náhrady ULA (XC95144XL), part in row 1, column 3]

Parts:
C1, C4, C5, C6, C7, C8, C9, C10: 100n; C_0805_2012Metric
C2: 10u; C_1206_3216Metric
C3: 22u; C_1206_3216Metric
J1: do patice ULA (precizní kolíky); DIP-40_W15.24mm
J2: RGB + zvuk + napájení (na J8 hlavní desky); PinHeader_1x10_P2.54mm_Vertical
J3: JTAG; PinHeader_1x06_P2.54mm_Vertical
R1: 1k; R_0805_2012Metric
R2, R3, R4, R5: 10k; R_0805_2012Metric
U1: XC95144XL-10TQG100C; TQFP-100_14x14mm_P0.5mm
U2: AMS1117-3.3; SOT-223-3_TabPin2
X1: 14.000 MHz 3,3V; Oscillator_SMD_Abracon_ASE-4Pin_3.2x2.5mm

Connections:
+3V3: C1.1, C3.1, C4.1, C5.1, C6.1, C7.1, C8.1, C9.1, C10.1, J3.1, R3.1, R4.1, U1.5 (VCCINT), U1.26 (VCCIO), U1.38 (VCCIO), U1.51 (VCCIO), U1.57 (VCCINT), U1.88 (VCCIO), U1.98 (VCCINT), U2.2 (VOUT), X1.1 (EN), X1.4 (VDD)
+5V: C2.1, J1.14 (VCC), J2.7, U2.3 (VIN)
A14: J1.36 (A14), U1.15 (FB1_15)
A15: J1.37 (A15), U1.16 (FB1_16)
BEEP: J2.9, U1.35 (FB5_35)
CAS_n: J1.1 (~CAS), U1.25 (FB3_25)
CLK14: U1.22 (FB1_22/GCK1), X1.3 (OUT)
CSYNC_n: J2.5, U1.67 (FB8_67)
D0: J1.18 (D0), U1.74 (FB6_74)
D1: J1.21 (D1), U1.76 (FB6_76)
D2: J1.22 (D2), U1.77 (FB6_77)
D3: J1.25 (D3), U1.78 (FB6_78)
D4: J1.27 (D4), U1.79 (FB6_79)
D5: J1.29 (D5), U1.80 (FB6_80)
D6: J1.30 (D6), U1.81 (FB6_81)
D7: J1.31 (D7), U1.82 (FB6_82)
DRAM_P5: J1.5 (DRAM_P5), U1.91 (FB4_91)
DRAM_P6: J1.6 (DRAM_P6), U1.90 (FB4_90)
DRAM_P7: J1.7 (DRAM_P7), U1.89 (FB4_89)
DRAM_P8: J1.8 (DRAM_P8), U1.92 (FB4_92)
DRAM_P9: J1.9 (DRAM_P9), U1.93 (FB4_93)
DRAM_P10: J1.10 (DRAM_P10), U1.94 (FB4_94)
DRAM_P11: J1.11 (DRAM_P11), U1.95 (FB4_95)
EAR_IN: R2.2, U1.2 (FB2_2/GTS4)
GND: C1.2, C2.2, C3.2, C4.2, C5.2, C6.2, C7.2, C8.2, C9.2, C10.2, J2.8, J2.10, J3.2, R5.2, U1.21 (GND), U1.31 (GND), U1.44 (GND), U1.62 (GND), U1.69 (GND), U1.75 (GND), U1.84 (GND), U1.100 (GND), U2.1 (GND), X1.2 (GND)
INT_n: J1.12 (~INT), U1.17 (FB1_17)
IORQGE_n: J1.33 (~IORQGE), U1.14 (FB1_14)
KB1: J1.26 (KB1), U1.6 (FB2_6)
KB2: J1.24 (KB2), U1.7 (FB2_7)
KB3: J1.23 (KB3), U1.8 (FB2_8)
KB4: J1.20 (KB4), U1.9 (FB2_9)
KB5: J1.19 (KB5), U1.10 (FB2_10)
MG: J1.28 (MG), R1.2, R2.1
MIC_OUT: R1.1, U1.1 (FB2_1/GTS3)
MREQ_n: J1.38 (~MREQ), U1.13 (FB1_13)
PHI_CPU: J1.32 (Φ), U1.19 (FB1_19)
RAS_n: J1.35 (~RAS), U1.24 (FB3_24)
RD_n: J1.3 (~RD), U1.11 (FB1_11)
ROMCS_n: J1.34 (~ROMCS), U1.18 (FB1_18)
TCK: J3.3, R5.1, U1.48 (TCK)
TDI: J3.5, R4.2, U1.45 (TDI)
TDO: J3.4, U1.83 (TDO)
TMS: J3.6, R3.2, U1.47 (TMS)
VID_B: J2.3, U1.65 (FB8_65)
VID_G: J2.2, U1.64 (FB8_64)
VID_I: J2.4, U1.66 (FB8_66)
VID_R: J2.1, U1.63 (FB8_63)
VSYNC_n: J2.6, U1.68 (FB8_68)
WE_n: J1.4 (~WE), U1.28 (FB3_28)
WR_n: J1.2 (~WR), U1.12 (FB1_12)

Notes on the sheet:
DIDAKTIK GAMA – MODUL NÁHRADY ULA (XC95144XL)
Spoje jsou vedeny návěštími (labels) – stejné jméno = stejný net. ~{X} = aktivní v nule.
K OVĚŘENÍ (na předloze nečitelné / odhadnuté):
• GND modulu: zem a +5 V přicházejí kabelem přes J2 z J8 hlavní desky – Pin GND ULA není na předloze Gamy ani ve schématu Spectra čitelný – na J1 není GND zapojen
• DRAM_P5..P11: adresové výstupy podle pinů ULA (Gama: pin 7 = A0, 6 = A1, 5 = A2) – Ve schématu Spectra je pořadí jiné (pin 5 = A0) – firmware musí vydávat bity podle zapojení multiplexeru v Gamě
• U1 firmware: zx_ula (OpenCores, GPL) s přiřazením pinů z ula_cpld_modul.ucf – Názvy portů v HDL namapovat na názvy netů v UCF; hodiny 14 MHz na GCK1 (pin 22)
• MG pin 28: výstup MIC přes 1k, vstup EAR přes 10k – Prahy vstupu CPLD (LVTTL) se liší od ULA – při potížích s nahráváním doplnit Schmittův klopný obvod
• BEEP (pin 35): firmware musí na BEEP vydávat bit 4 portu FE (reproduktor) – Doplnit do HDL jako samostatný výstup; MIC/EAR na pinu 28 zůstává pro magnetofon
• J1: kolíky do patice ULA – Použít precizní (soustružené) kolíky; modul nesmí narazit na okolní součástky

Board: 2 copper layers, 21 parts (0 on the bottom side), 50 nets, no tracks yet.

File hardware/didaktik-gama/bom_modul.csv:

skupina,hodnota,pocet,reference,pouzdro
CPLD,XC95144XL-10TQG100C,1,U1,Package_QFP:TQFP-100_14x14mm_P0.5mm
Kondenzátor,100n,8,C1 C4 C5 C6 C7 C8 C9 C10,Capacitor_SMD:C_0805_2012Metric
Kondenzátor,10u,1,C2,Capacitor_SMD:C_1206_3216Metric
Kondenzátor,22u,1,C3,Capacitor_SMD:C_1206_3216Metric
Konektor,JTAG,1,J3,Connector_PinHeader_2.54mm:PinHeader_1x06_P2.54mm_Vertical
Konektor,RGB + zvuk + napájení (na J8 hlavní desky),1,J2,Connector_PinHeader_2.54mm:PinHeader_1x10_P2.54mm_Vertical
Konektor,do patice ULA (precizní kolíky),1,J1,Package_DIP:DIP-40_W15.24mm
Napájení,AMS1117-3.3,1,U2,Package_TO_SOT_SMD:SOT-223-3_TabPin2
Ostatní,"14.000 MHz 3,3V",1,X1,Oscillator:Oscillator_SMD_Abracon_ASE-4Pin_3.2x2.5mm
Rezistor,10k,4,R2 R3 R4 R5,Resistor_SMD:R_0805_2012Metric
Rezistor,1k,1,R1,Resistor_SMD:R_0805_2012Metric

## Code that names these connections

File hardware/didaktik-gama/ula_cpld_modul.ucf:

# Didaktik Gama – modul náhrady ULA, XC95144XL-10TQ100 (generováno gen.py)
NET "MIC_OUT" LOC = "P1";
NET "EAR_IN" LOC = "P2";
NET "KB1" LOC = "P6";
NET "KB2" LOC = "P7";
NET "KB3" LOC = "P8";
NET "KB4" LOC = "P9";
NET "KB5" LOC = "P10";
NET "RD_n" LOC = "P11";
NET "WR_n" LOC = "P12";
NET "MREQ_n" LOC = "P13";
NET "IORQGE_n" LOC = "P14";
NET "A14" LOC = "P15";
NET "A15" LOC = "P16";
NET "INT_n" LOC = "P17";
NET "ROMCS_n" LOC = "P18";
NET "PHI_CPU" LOC = "P19";
NET "CLK14" LOC = "P22";
NET "RAS_n" LOC = "P24";
NET "CAS_n" LOC = "P25";
NET "WE_n" LOC = "P28";
NET "BEEP" LOC = "P35";
NET "VID_R" LOC = "P63";
NET "VID_G" LOC = "P64";
NET "VID_B" LOC = "P65";
NET "VID_I" LOC = "P66";
NET "CSYNC_n" LOC = "P67";
NET "VSYNC_n" LOC = "P68";
NET "D0" LOC = "P74";
NET "D1" LOC = "P76";
NET "D2" LOC = "P77";
NET "D3" LOC = "P78";
NET "D4" LOC = "P79";
NET "D5" LOC = "P80";
NET "D6" LOC = "P81";
NET "D7" LOC = "P82";
NET "DRAM_P7" LOC = "P89";
NET "DRAM_P6" LOC = "P90";
NET "DRAM_P5" LOC = "P91";
NET "DRAM_P8" LOC = "P92";
NET "DRAM_P9" LOC = "P93";
NET "DRAM_P10" LOC = "P94";
NET "DRAM_P11" LOC = "P95";
NET "CLK14" TNM_NET = "CLK14";
TIMESPEC "TS_CLK14" = PERIOD "CLK14" 71.4 ns HIGH 50%;

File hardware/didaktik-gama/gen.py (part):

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   [P(34, "D0"), P(33, "D1"), P(32, "D2"), P(31, "D3"), P(30, "D4"), P(29, "D5"), P(28, "D6"), P(27, "D7"), None,
    P(5, "~{RD}"), P(36, "~{WR}"), P(9, "A0"), P(8, "A1"), P(6, "~{CS}"), P(35, "RESET"), None,
    P(26, "VCC", PW), P(7, "GND", PW)],
   [P(4, "PA0"), P(3, "PA1"), P(2, "PA2"), P(1, "PA3"), P(40, "PA4"), P(39, "PA5"), P(38, "PA6"), P(37, "PA7"),
    None] + [P(18 + i, f"PB{i}") for i in range(8)] + [None] +
   [P(14, "PC0"), P(15, "PC1"), P(16, "PC2"), P(17, "PC3"), P(13, "PC4"), P(12, "PC5"), P(11, "PC6"), P(10, "PC7")])
ic("ULA",
   [P(3, "~{RD}"), P(2, "~{WR}"), P(38, "~{MREQ}"), P(33, "~{IORQGE}"), P(12, "~{INT}"), P(34, "~{ROMCS}"),
    P(36, "A14"), P(37, "A15"), P(32, "Φ"), None,
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
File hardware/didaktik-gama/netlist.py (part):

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    16: "D4", 17: "D5", 18: "D6", 19: "D7", 20: "/ROMCS", 21: "A10",
    22: "/RD", 23: "A11", 24: "A9", 25: "A8", 26: "A13", 27: "+5V", 28: "+5V"})
C("C2", "100p", "/ROMCS", "GND")
verify.append(("U2 pin 20 (/CE)", "/ROMCS = ULA pin 34",
               "U pinu 20 je jen kondenzátor 100p; připojení na ULA ROMCS je odhad"))

# ---------------------------------------------------------------- 8255
pa = {0: 4, 1: 3, 2: 2, 3: 1, 4: 40, 5: 39, 6: 38, 7: 37}
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    pico[gp_pin[i]] = f"KBD_A{8 + i}"          # GP0..GP7 = A8..A15 (3,3 V)
for i in range(5):
    pico[gp_pin[8 + i]] = f"KBD_KB{i + 1}"     # GP8..GP12 -> KB1..KB5 (přes 74LVC07)
pico[gp_pin[13]] = "KBD_RST"                   # GP13 -> /RESET (Ctrl+Alt+Del)
pico[gp_pin[14]] = "KBD_TAPE"                  # GP14 -> signál kazety (přehrávač .TAP z USB disku)
add("U39", "PICO", "Raspberry Pi Pico (USB host)", "gama:RaspberryPi_Pico_THT", pico)
add("U40", "74LVC245", "74LVC245", "Package_SO:SOIC-20W_7.5x12.8mm_P1.27mm", {
    1: "+3V3_KBD", 19: "GND", 10: "GND", 20: "+3V3_KBD",
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# piny 2118 podle čísel u vodičů na předloze
p2118_addr = {"VA3": 13, "VA4": 12, "VA5": 10, "VA6": 6, "VA0": 5, "VA1": 11, "VA2": 7}
for i in range(8):
    pins = {1: None, 2: VD[i], 14: VD[i], 3: "/VWE", 4: "/VRAS", 15: "/VCAS",
            8: "+5V", 9: "+5V", 16: "GND"}
    for net, p in p2118_addr.items():
        pins[p] = net
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                      12: ("A1", "A9", "RA1"), 7: ("A0", "A8", "RA0")})
mux157("U6", "MUX2", {12: ("A6", "A14", "RA6"), 4: ("A5", "A13", "RA5"),
                      7: ("A4", "A12", "RA4"), 9: ("A3", "A11", "RA3")})
verify.append(("U5 pin 10", "sloupcový bit RA7 = BANK (PC0 8255)",
               "Funkční odhad: horních 32K je 2x32K banka přepínaná PC0"))

# 8x4164 (2x32K banka 8000h-FFFFh)
p4164_addr = {0: 5, 1: 7, 2: 6, 3: 12, 4: 11, 5: 10, 6: 13, 7: 9}
for i in range(8):
    pins = {1: None, 2: D[i], 14: D[i], 3: "/WE64", 4: "/RAS64", 15: "/CAS64",
            8: "+5V", 16: "GND"}
    for b, p in p4164_addr.items():
        pins[p] = RA[b]
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    13: "/RESET", 12: "RESET",                           # RESET pro 8255
    11: None, 10: None, 7: "GND", 14: "+5V"})
add("U26", "7404", "74LS04", "Package_DIP:DIP-14_W7.62mm", {
    1: "PC0", 2: "BANK", 11: "BANK", 10: "/BANKSEL",
    3: "A1", 4: "A1_N",                                          # dekódování AY (A1 = 0)
    5: None, 6: None, 9: None, 8: None, 13: None, 12: None,
    7: "GND", 14: "+5V"})
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add("C60", "CP", "47u/10V", "Capacitor_THT:CP_Radial_D5.0mm_P2.00mm", {1: "+5V", 2: "GND"})
add("C61", "CP", "47u/10V", "Capacitor_THT:CP_Radial_D5.0mm_P2.00mm", {1: "+5V", 2: "GND"})
verify.append(("C20–C61", "blokování napájení",
               "Doplněno: 100n u každého IC (u napájecích pinů), 47u u bank 4164 a 2118"))

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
